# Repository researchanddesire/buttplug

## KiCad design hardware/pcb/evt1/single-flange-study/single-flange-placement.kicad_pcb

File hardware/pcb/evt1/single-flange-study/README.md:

# Single flange PCB study

This separate, unrouted candidate combines the existing flange electronics, fixed compass and four PCB-mounted charge/data targets on **one flange PCB**. The existing body PCB, charger, power rails, motor driver, tip-temperature sensing and protection circuits remain unchanged. It does not consolidate the body electronics into the flange.

`single-flange-placement.kicad_pcb` contains 35 retained source positions and four new Mill-Max1946 fixed targets. The 35 positions retain every selected pad/drill, Fab outline, courtyard, antenna keepout and schematic pad net. Only assembly silk is deferred and package models are linked locally. `J1` contact wire lands become four actual through-hole targets; sensor-only `J82` interboard lands are unnecessary after its circuit joins the flange. The existing body `J81` lands remain untouched. There are no tracks or vias and no new fabrication files.

## Physical arrangement

The editable KiCad outline is82×26×1mm, within the fixed88×32mm flange cross-section. Its left edge opens beneath the actual integrated antenna; two R2 edge reliefs preserve the existing case screw axes at X12/Z±13. Four provisionalØ1.6 mounts lie at (−30,−10), (−38,+10), (+38,−10), (+38,+10), in product X/Z millimetres.

The joint mechanical study adds3.2mm behind the original rigid rear face. The PCB F surface is productY−26.952 and B is−25.952. Parts face inward on B; only the two Omron B3U buttons and four fixed targets face outward on F. The requested battery growth envelope ends atY−22.6. Conservative selected heights leave at least1.902mm between the populated B-side parts above that envelope and the growth envelope, before unqualified solder stand-off and received tolerances; the tall J4/J7 headers are to its left. Received pack dimensions, tolerances, insulation and retention remain separate checks.

| Interface | Product X/Z centres | Detail |
| --- | --- | --- |
| Targets | (−16,10), (−10,10), (−4,10), (+2,10) | GND/D−/D+/5V;6mm pitch; Mill-Max1946-0-00-15-00-00-03-0 |
| Buttons | (−17,0), (−9,0) | Existing Power/Mode circuits and selected B3U-1000P retained |
| Compass | (33,0) | LSM303AGR on B; new proper rigid package-to-flange registration is required |
| Radio | (−30,0) footprint origin | Existing ESP32-C3-MINI-1-N4X with its integrated PCB antenna toward the left end |

Mounting screws are not part of the39 electrical package models. The left mounts are inside the antenna clearance region and require nonmetal hardware; the existing NBK RENY candidate still needs actual engagement/strength checks in the mechanical study. Do not describe that region as metal-clear while metallic screws are fitted.

The1946 has a nominal3.048mm face height and2.794mm tail below its seating shoulder; its target face isY−30.0. The manufacturer catalog gives length tolerance±0.127mm and diameter tolerance±0.0508mm. The recommendedØ0.8636 mounting hole is retained; theØ3.2 copper land is an engineering choice requiring supplier/assembly acceptance. The B-sideØ4 annular plastic bearing posts and four nominal tails must be included in mechanical checks. PCB/solder flex is not credited for docking force.

The joint mechanical candidate uses a permanent pre-cured common diaphragm/web between PCB and rear cover, covering F-side X−20.7..+4.7/Z−3.15..12.65, with two closed switch cups and four contact necks. No other F-side part is placed there. Molding barriers, compatible materials, force/travel, shaft tolerances and electrical/sealing processes remain unqualified.

## Electrical conservation and remaining work

`interface-contract.json` records the unchanged numeric1:1 J6/J7 body interface, preserved U81 nets, recovery and four-contact substitutions. TPS3422 hardware reset, Power/Mode/BOOT recovery, USBLC6,22Ω data resistors, input PTC/diode, pullups and decoupling remain present. The body-to-flange loom remains; the former separate sensor loom can be removed only when its assembly documentation and new merged schematic are implemented.

The board is a placement study. Native DRC has zero placement violations with every check enabled;120 unconnected items are expected. New merged schematic/ERC, intentional power and ground returns, USB routing/ESD, local decoupling, routing/DRC, stock/service access and fabrication outputs remain to do. The supplied39 package models include the actual103-solid Espressif OEM model, a primary-dimensioned1946 profile and KiCad nominal selected package families. Manufacturer maximum dimensions remain separate from nominal STEP geometry. Every model must pass the cold geometry/pose checks before mechanical acceptance.

The MINI-1 has no host coax/RF feed. Its antenna region X−41..−35.6/Z±6.6 is outside the host board and excludes all four copper layers. The pack is42.35mm away horizontally. The joint study moves steel keepers away from this end. Espressif's15mm all-direction housing-clearance guidance is **not fully met** by this current component arrangement; C31/C32 remain near the module's VDD edge, while avoidable22Ω and diode positions have been moved beyond15mm. C31's3V3 land is2.15mm and C32's3V3 land3.483mm from U6pad3; route short supply/return paths with adjacent ground vias. Resolve or explicitly qualify this near-pin RF tradeoff, enclosure/overmold loading, received module/pack and final range/throughput before claiming RF performance. Keep motor/charging current returns away from the compass; new assembly calibration and an actual magnetic survey remain required.

[Espressif module datasheet](https://www.espressif.com/sites/default/files/documentation/esp32-c3-mini-1_datasheet_en.pdf), [Espressif module positioning guidance](https://docs.espressif.com/projects/esp-hardware-design-guidelines/en/latest/esp32c3/pcb-layout-design.html), [Mill-Max catalog, printed page223.1](https://www.mill-max.com/sites/default/files/external/catalog/2020-01/202-246_3.pdf).

## Review and rebuild

`mcad.json` binds every model file/hash and proper model-to-product4×4 transform. `SingleFlangePlacement.FCStd` has an editable, fully constrained PCB outline/drill sketch and native1mm Pad, plus39 links to actual imported selected-part bodies. `SingleFlangePlacement.step` follows those explicit F/B planes. `NativeKiCadPlacement.step` is the independent raw KiCad export at origin100×100mm; its FR4 and solder/mask seating offsets differ, so do not apply a single rigid height correction to use it as finished-board clearance proof. `native-step-pose-checks.json` records those exact layer offsets. No model is reflected.

Run `build_study.py` with the installed KiCad Python only to deliberately regenerate this unrouted study. Run native KiCad10 DRC, export STEP at origin100×100mm, `export_mcad.py`, `check_study.py`, `check_oem_model.py` and `check_native_step.py` for the source,159+4 pad,61 module-contact and actual package-geometry audits. `source-inventory.json` binds all original device artwork/netlists/parts data. Original product natives, routed device/dock boards and the human-owned BOM remain unchanged. No print, assembly, power, radio, sealing or build release is claimed.

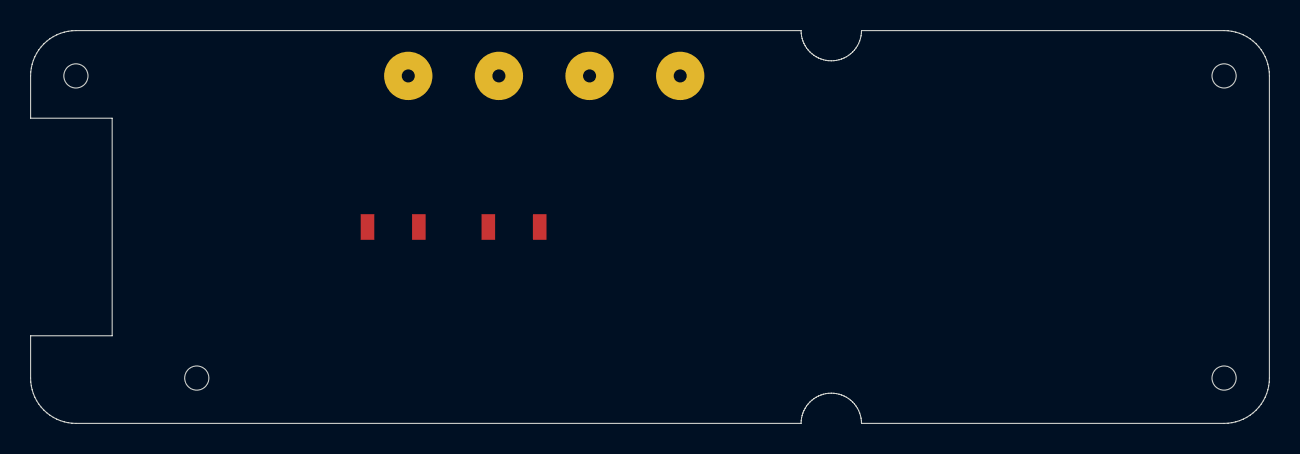
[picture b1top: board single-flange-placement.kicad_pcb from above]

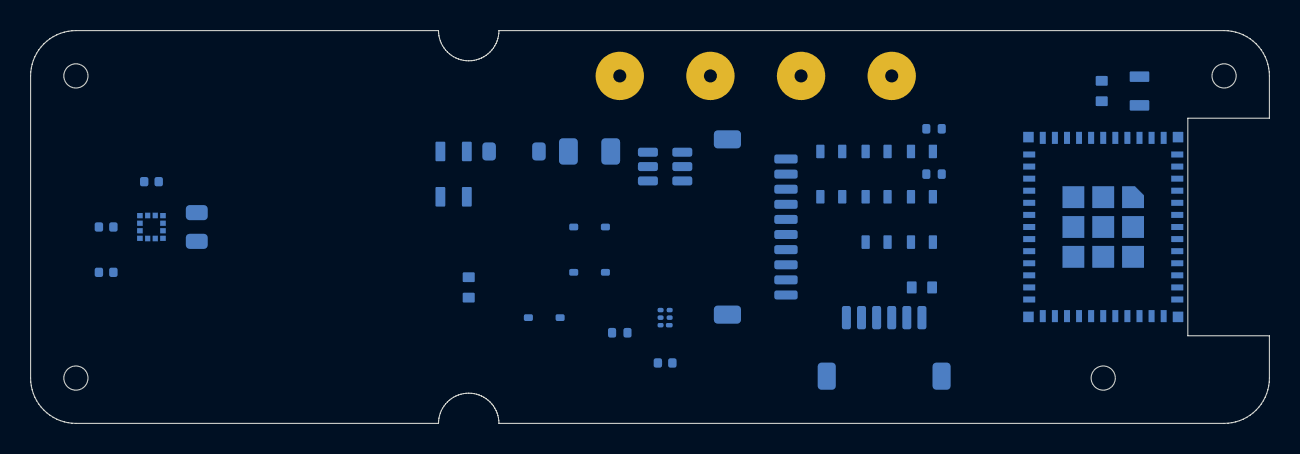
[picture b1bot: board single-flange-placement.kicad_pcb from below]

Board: 4 copper layers, 82.0 x 26.0 mm, 43 parts (33 on the bottom side), 26 nets, no tracks yet.

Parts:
C31: 10uF 10V; Murata_GRM21_0805_Reflow
C32, C34: 100nF; Murata_GRM18_0603_Reflow
C33: 1uF; TDK_C1608_0603_Reflow
C71, C82: 100nF; C_0402_1005Metric
C81: 220nF; C_0402_1005Metric
C83: 22uF 10V / Ceff>=10uF at3V3; C_0805_2012Metric
C84: 100nF / VDDIO local; C_0402_1005Metric
CT1, CT2, CT3, CT4: 1946-0-00-15-00-00-03-0; MillMax_1946_0_PTH_Study
D1: Schottky 1A/20V candidate; Diodes_B140HW_SOD123_A1_K2
D71, D72, D73: BAT54WS-E3-08; D_SOD-323
F1: PTC 500mA candidate; Fuse_1206_3216Metric
J4: SERVICE_USB_BOOT; JST_SH_SM06B-SRSS-TB_1x06-1MP_P1.00mm_Horizontal
J7: SM10B-SRSS-TB candidate; JST_SH_SM10B-SRSS-TB_1x10-1MP_P1.00mm_Horizontal
MH1, MH2, MH3, MH4: PROVISIONAL M1.4 support
R31, R32, R33, R34, R35, R36: 10k; Vishay_TNPW0603_IEC_Reflow
R37, R38: 4.7k; Vishay_TNPW0603_IEC_Reflow
R39, R40: 1.00M 1%; Vishay_TNPW0805_IEC_Reflow
R71: 10k; R_0402_1005Metric
R75, R76: 22R; R_0402_1005Metric
SW1: POWER / momentary; SW_SPST_B3U-1000P
SW2: MODE / momentary; SW_SPST_B3U-1000P
U6: ESP32-C3-MINI-1-N4X candidate; Espressif_ESP32-C3-MINI-1_53Pads
U71: TPS3422EGDRYR; Texas_USON-6_1x1.45mm_P0.5mm_SMD
U75: USBLC6-2SC6; SOT-23-6
U81: LSM303AGRTR; LGA-12_2x2mm_P0.5mm

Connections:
3V3: C31.1, C32.1, C71.1, C82.1, C83.1, C84.1, J7.3, R31.1, R32.1, R33.1, R34.1, R35.1, R36.1, R37.1, R38.1, R71.1, U6.3, U71.4, U81.2, U81.3, U81.9, U81.10
BOOT_N: D73.2, J4.5, R34.2, U6.23
DOCK_5V: CT4.1, F1.1, U75.5
DOCK_FUSED: D1.1, F1.2
DOCK_PRESENT_N: D72.1, J7.7, U6.30
GND: C31.2, C32.2, C33.2, C34.2, C71.2, C81.2, C82.2, C83.2, C84.2, CT1.1, J4.1, J7.1, R40.2, SW1.2, SW2.2, U6.1, U6.2, U6.11, U6.14, U6.36, U6.37, U6.38, U6.39, U6.40, U6.41, U6.42, U6.43, U6.44, U6.45, U6.46, U6.47, U6.48, U6.49, U6.50, U6.51, U6.52, U6.53, U71.2, U71.5, U71.6, U75.2, U81.6, U81.8
I2C_SCL: J7.9, R38.2, U6.19, U81.1
I2C_SDA: J7.8, R37.2, U6.18, U81.4
MAG_C1: C81.1, U81.5
MCU_EN: C33.1, J4.4, R31.2, U6.8, U71.1
MODE_N: D73.1, R36.2, SW2.1, U6.6
MOTOR_ARM: J7.5, U6.21
MOTOR_PWM: J7.6, U6.20
PACK_P: J7.4, R39.1
POWER_N: D71.2, D72.2, R35.2, U6.13
POWER_SWITCH_N: D71.1, R71.2, SW1.1, U71.3
STRAP2: R32.2, U6.5
STRAP8: R33.2, U6.22
TIP_EXC_EN: J7.10, U6.16
UART_TX: J4.6, U6.31
USB_DM: J4.2, R75.2, U6.26
USB_DM_CONTACT: CT2.1, R75.1, U75.1, U75.6
USB_DP: J4.3, R76.2, U6.27
USB_DP_CONTACT: CT3.1, R76.1, U75.3, U75.4
VBAT_ADC: C34.1, R39.2, R40.1, U6.12
VBUS_CHG: D1.2, J7.2

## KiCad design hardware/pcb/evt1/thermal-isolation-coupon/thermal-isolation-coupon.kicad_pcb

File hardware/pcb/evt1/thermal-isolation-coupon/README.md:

# Compass EVT1 thermal isolation comparison coupon

This 48 × 30 mm standalone coupon compares two 6 × 6 mm pad sites. Site A keeps the laminate intact with a local copper-pour keepout. Site B uses the same keepout and a routed 1.2 mm-wide cavity around the sensor head and most of its neck. The neck is nominally 1.2 mm wide and 8.0 mm from the head shoulder to the end of the route. Inside corners have 0.5 mm nominal radius. The 7.2 × 8.0 mm head supports the nominal pad footprint. Both sensors and their equal-length 0.15 mm routes sit on B.Cu. The part is Vishay NTCS0402E3103FL1T. The land pattern matches Vishay's reflow dimensions. [Vishay part data](https://www.vishay.com/docs/29003/ntcs0402e3t.pdf) · [Mounting and solder pads](https://www.vishay.com/docs/29224/handlmount-ntcssmdntctherm.pdf)

| Site | Sensor center, PCB coordinates | Manual lands | Population |
|---|---|---|---|
| A, intact laminate | (12.0, 11.5) mm | J901.1 sense and J901.2 return | TH901 on B.Cu |
| B, routed | (36.0, 11.5) mm | J902.1 sense and J902.2 return | TH902 on B.Cu |

The pins are electrically independent. TP901 anchors In1, In2 and B ground pours through one plated via. It can float during resistance measurements. Each sensor has its own return and neither return connects to TP901. The fixture holes are 2.2 mm nominal at (3.0, 27.0) and (45.0, 27.0) mm. Fixture loads belong at the base of the board.

## Fabrication input

Submit `thermal-isolation-coupon-fabrication.zip` as the Gerber and drill archive. Specify four-layer FR4, **1.0 mm finished thickness**, ENIG and **35 µm nominal finished copper on all four layers**, matching the active flange stack request. The nominal dielectrics are 0.10 mm / 0.64 mm / 0.10 mm. Ask the board shop to confirm the stack and the 1.2 mm isolation cavity with the 0.5 mm corner radii before releasing fabrication. The interior closed shape is unplated through routing from the Edge.Cuts Gerber. The separate NPTH drill contains two fixture holes. Keep the two thin traces at least 0.25 mm from the routed edges. CAM must preserve the neck and cavity as drawn. An example board shop lists a 1.0 mm minimum non-plated slot width. [Fabrication capability reference](https://jlcpcb.com/capabilities/Capabilities)

For SMT assembly provide `assembly-parts.csv` and `placements.csv`. Populate TH901 and TH902 only. The position file follows the native KiCad bottom-placement convention, with negative Y coordinates relative to the Gerber origin. J901/J902 are hand-wired lands and TP901 is a bare plane anchor. Use a supporting carrier during assembly and handling. Receive one bare witness board to inspect routed width, the neck and the mask openings before handling an assembled coupon.

## Measurement

Use the two sites with the same dry inert pouch surrogate, pad material, actual gap and pack-facing surface temperature. Clamp the common base against the same temperature-controlled fixture. Measure the PCB temperature beside each neck root and the pouch surface under each site. Compare settled resistance-derived temperatures and transient response while holding the surrogate at 0 °C and heating the board base to 20 °C. Include the reverse gradient with a warmer pouch surrogate. The preliminary signed error allocation is 1.5 °C, so 7.5% PCB coupling alone would consume that budget in the 20 °C gradient. Record contact footprint, drift, lifted-pad behavior and neck deflection. Prevent pad material from bridging the routed gap to the surrounding board. Use fixture stops to carry the closure load. Measure pad contact force and neck deflection. Keep compression off the thermistor body. If the head needs a backing support, use the same support at both sites and characterize the extra heat path it introduces.

The test can compare isolation in a controlled fixture. The actual flange still needs its own thermal and electrical cutoff checks with the seated stack, including the pack-to-PCB gradient and possible pad contact loss. [Vishay mounting load guidance](https://www.vishay.com/docs/29224/handlmount-ntcssmdntctherm.pdf)

## Verification

The saved board passed the KiCad 7.0.7 Python DRC with zero violations, zero unconnected pads and zero footprint errors. Gerbers, separate PTH and NPTH Excellon, and the bottom placement CSV were exported from that board with KiCad 7.0.7. A saved-board readback verified a closed routed loop, the four separate sensor nets and no GND fill at the sampled locations across either pad footprint. Supplier CAM, assembly and thermal performance remain unverified. The local `ThermalCoupon.pretty` library is bound through `fp-lib-table`.

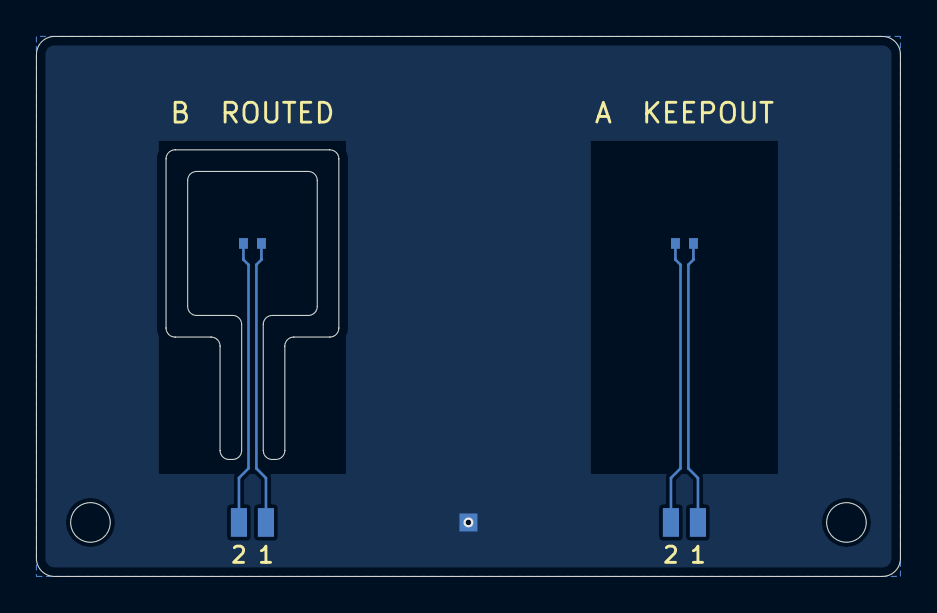
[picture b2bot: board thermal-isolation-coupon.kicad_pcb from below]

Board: 4 copper layers, 48.0 x 30.0 mm, 7 parts (7 on the bottom side), 4 nets.

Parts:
H901, H902: 2.2 mm fixture hole; MountingHole_2p2mm
J901, J902: Two isolated solder tabs; Dual_Wire_0p9x1p6
TH901, TH902: NTCS0402E3103FL1T; Vishay_NTCS0402_Reflow
TP901: Plane anchor; Plane_Anchor

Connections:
A_RETURN: J901.2, TH901.2
A_SENSE: J901.1, TH901.1
B_RETURN: J902.2, TH902.2
B_SENSE: J902.1, TH902.1
